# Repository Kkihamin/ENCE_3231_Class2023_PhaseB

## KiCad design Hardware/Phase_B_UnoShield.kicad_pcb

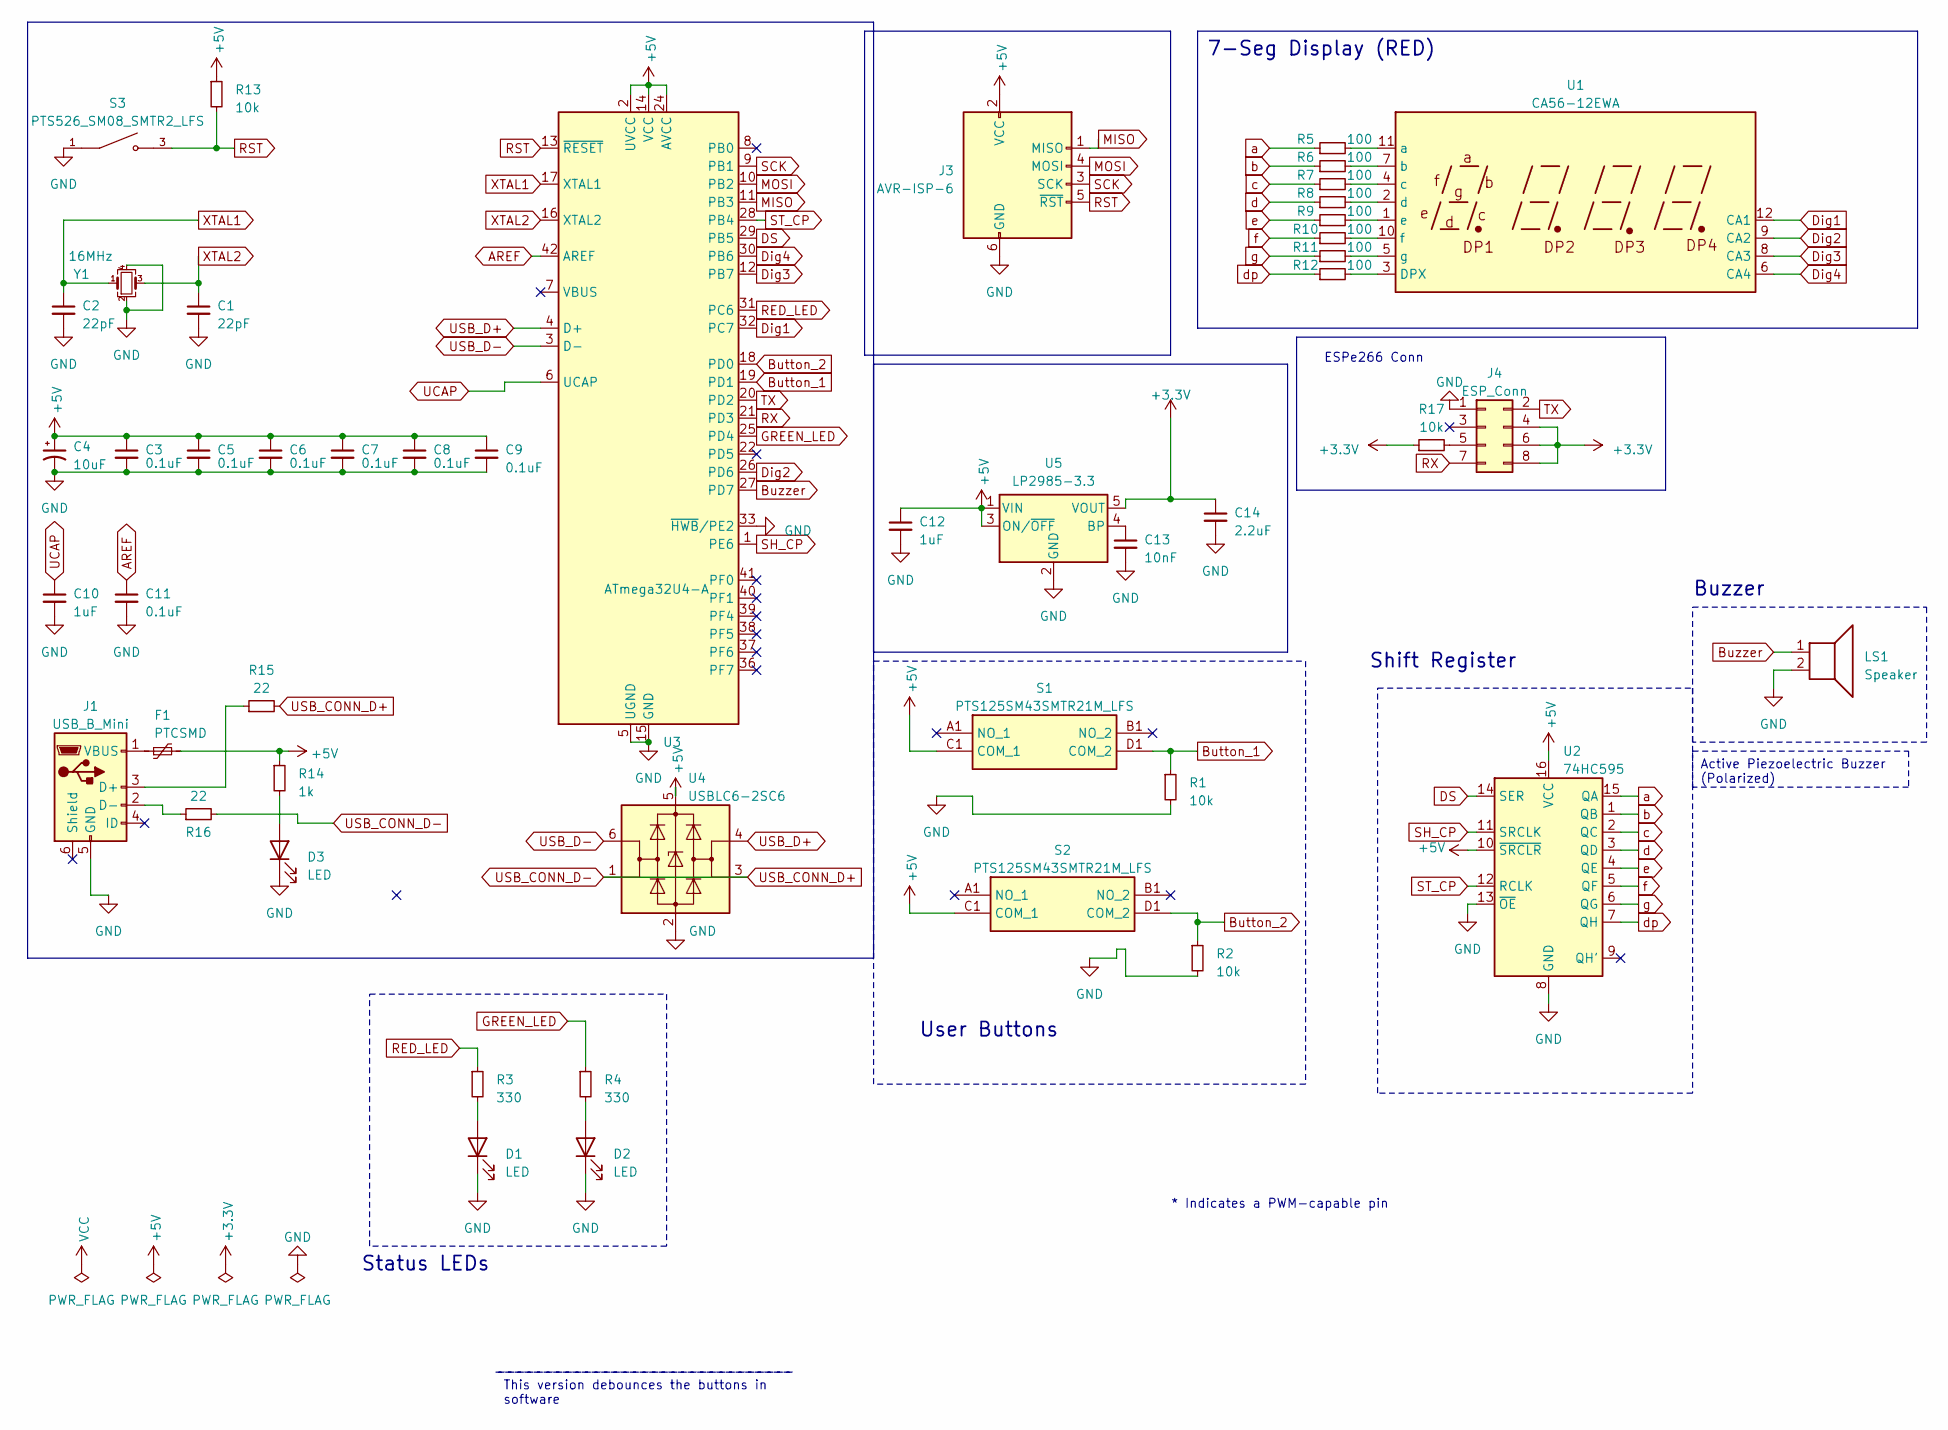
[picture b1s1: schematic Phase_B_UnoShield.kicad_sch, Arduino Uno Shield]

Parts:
C1, C2: 22pF; C_0603_1608Metric
C3, C5, C6, C7, C8, C9: 0.1uF; C_0805_2012Metric
C4: 10uF; C_0603_1608Metric
C10, C12: 1uF; C_0201_0603Metric
C11: 0.1uF; C_0201_0603Metric
C13: 10nF; C_0201_0603Metric
C14: 2.2uF; C_0201_0603Metric
D1, D2, D3: LED; LED_0805_2012Metric
F1: PTCSMD; Fuse_1812_4532Metric
J1: USB_B_Mini; USB_Mini-B_Lumberg_2486_01_Horizontal
J3: AVR-ISP-6; PinHeader_2x03_P2.54mm_Vertical
J4: ESP_Conn; PinSocket_2x04_P2.54mm_Vertical
LS1: Speaker; Buzzer_12x9.5RM7.6
R1, R2, R13, R17: 10k; R_0603_1608Metric
R3, R4: 330; R_0805_2012Metric
R5, R6, R7, R8, R9, R10, R11, R12: 100; R_0805_2012Metric
R14: 1k; R_0805_2012Metric
R15: 22; R_0603_1608Metric
R16: 22; R_0201_0603Metric
S1, S2: PTS125SM43SMTR21M_LFS; PTS125_SMD_Button; Manufacturer_Part_Number PTS125SM43SMTR21M LFS; Mouser Part Number 611-PTS125S43SMTRLFS
S3: PTS526_SM08_SMTR2_LFS; PTS526_SMD_Button; PARTREV 20 mar 19
U1: CA56-12EWA
U2: 74HC595; TSSOP-16_4.4x5mm_P0.65mm
U3: ATmega32U4-A; TQFP-44_10x10mm_P0.8mm
U4: USBLC6-2SC6; SOT-23-6
U5: LP2985-3.3; SOT-23-5
Y1: 16MHz; Crystal_SMD_Abracon_ABM8G-4Pin_3.2x2.5mm

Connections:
+3.3V: C14.1, J4.4, J4.6, J4.8, R17.1, U5.5 (VOUT)
+5V: C3.1, C4.1, C5.1, C6.1, C7.1, C8.1, C9.1, C12.1, F1.2, J3.2 (VCC), R13.1, R14.1, S1.C1 (COM_1), S2.C1 (COM_1), U2.10 (~SRCLR), U2.16 (VCC), U3.2 (UVCC), U3.14 (VCC), U3.24 (AVCC), U3.34 (VCC), U3.44 (AVCC), U4.5 (VBUS), U5.1 (VIN), U5.3 (ON/~OFF)
AREF: C11.1, U3.42 (AREF)
Button_1: R1.1, S1.D1 (COM_2), U3.19 (PD1)
Button_2: R2.1, S2.D1 (COM_2), U3.18 (PD0)
Buzzer: LS1.1, U3.27 (PD7)
DS: U2.14 (SER), U3.29 (PB5)
Dig1: U1.12 (CA1), U3.32 (PC7)
Dig2: U1.9 (CA2), U3.26 (PD6)
Dig3: U1.8 (CA3), U3.12 (PB7)
Dig4: U1.6 (CA4), U3.30 (PB6)
GND: C1.2, C2.2, C3.2, C4.2, C5.2, C6.2, C7.2, C8.2, C9.2, C10.2, C11.2, C12.2, C13.2, C14.2, D1.1 (K), D2.1 (K), D3.1 (K), J1.5 (GND), J3.6 (GND), J4.1, LS1.2, R1.2, R2.2, S3.1, U2.8 (GND), U2.13 (~OE), U3.5 (UGND), U3.15 (GND), U3.23 (GND), U3.33 (~HWB/PE2), U3.35 (GND), U3.43 (GND), U4.2 (GND), U5.2 (GND), Y1.2, Y1.4
GREEN_LED: R4.1, U3.25 (PD4)
MISO: J3.1 (MISO), U3.11 (PB3)
MOSI: J3.4 (MOSI), U3.10 (PB2)
unnamed: D1.2 (A), R3.2
unnamed: D2.2 (A), R4.2
unnamed: D3.2 (A), R14.2
unnamed: J1.3 (D+), R15.1
unnamed: J1.2 (D-), R16.1
unnamed: F1.1, J1.1 (VBUS)
unnamed: J4.5, R17.2
unnamed: R12.2, U1.3 (DPX)
unnamed: R5.2, U1.11 (a)
unnamed: R6.2, U1.7 (b)
unnamed: R7.2, U1.4 (c)
unnamed: R8.2, U1.2 (d)
unnamed: R9.2, U1.1 (e)
unnamed: R10.2, U1.10 (f)
unnamed: R11.2, U1.5 (g)
unnamed: C13.1, U5.4 (BP)
RED_LED: R3.1, U3.31 (PC6)
RST: J3.5 (~RST), R13.2, S3.3, U3.13 (~RESET)
RX: J4.7, U3.21 (PD3)
SCK: J3.3 (SCK), U3.9 (PB1)
SH_CP: U2.11 (SRCLK), U3.1 (PE6)
ST_CP: U2.12 (RCLK), U3.28 (PB4)
TX: J4.2, U3.20 (PD2)
UCAP: C10.1, U3.6 (UCAP)
USB_CONN_D+: R15.2, R16.2, U4.1 (I/O1), U4.3 (I/O2)
USB_D+: U3.4 (D+), U4.4 (I/O2)
USB_D-: U3.3 (D-), U4.6 (I/O1)
XTAL1: C2.1, U3.17 (XTAL1), Y1.1
XTAL2: C1.1, U3.16 (XTAL2), Y1.3
a: R5.1, U2.15 (QA)
b: R6.1, U2.1 (QB)
c: R7.1, U2.2 (QC)
d: R8.1, U2.3 (QD)
dp: R12.1, U2.7 (QH)
e: R9.1, U2.4 (QE)
f: R10.1, U2.5 (QF)
g: R11.1, U2.6 (QG)

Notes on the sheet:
Active Piezoelectric Buzzer (Polarized)
This version debounces the buttons in software
Shift Register
ESPe266 Conn
Status LEDs
User Buttons
Buzzer
* Indicates a PWM-capable pin
7-Seg Display (RED)

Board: 2 copper layers, 48 parts (0 on the bottom side), 52 nets, no tracks yet.

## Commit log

2023-04-15 Schematic and PCB initial commit
2023-04-20 Initial Commit
    This includes the schematic from kicad, ibom, step file, pdf of the board, board in front, back, and 3-D view. I have also ran the DRC and reduced the size of the pcb under 100 millimeters which is u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
2023-04-23 made edits
    cause of clearance violations
2023-04-23 Edit version 2
2023-04-27 Folder rename
2023-04-27 Edits to Phase B
    I added enclosure and the schematic as a pdf
2023-04-29 edits on code
2023-05-01 Update ESP8266_Kitchen_Timer_Communication.ino
    Made edits to the kitchen timer
2023-05-02 Create Block diagram of schematic.PNG
    this is block diagram of schematic
2023-05-02 modified block diagram
2023-05-03 block diagram for code
2023-05-05 Create Embedded Systems Phase B Report.docx
    Report initial submit before the assembly
